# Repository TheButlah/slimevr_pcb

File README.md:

# slimevr_pcb
A collection of PCBs designed for SlimeVR full-body trackers

- [ferrous_slime](/hardware/ferrous_slime/) - A fully custom surface-mount PCB.
  Unlike most of the SlimeVR community, it uses the ESP32-C3, a newer and more
  powerful chip. Designed to be a more powerful development platform, as it natively
  supports JTAG debugging over USB, more compilers and languages, including Rust,
  and supports Bluetooth LE v5.0.
  
- [breakout_slime](/hardware/breakout_slime/) - A through-hole PCB for use with
  breakout boards. Simplest and easy to assemble by hand, but not as small of a
  form factor as it could be.

## License
**This hardware is licensed under the CERN-OHL-P v2 license**, which is a permissive,
non-viral and non-reciprocal open hardware license. Unlike software licenses like
MIT and Apache 2.0, it better handles the nuances of hardware and protects both
the licensor and licensee from patent lawsuits.

**Unless you explicitly state otherwise, any contribution intentionally submitted
for inclusion in this work by you, shall be licensed as above, without any
additional terms or conditions.**

### Conveying notice of License
Note that as part of the CERN-OHL-P v2 license, recipients of manufactured
hardware must also receive notice of the above license. One such
method of conveying the notice is to include a link to the original source repo,
or printing "Licensed under CERN-OHL-P v2" on the PCB silkscreen. For more info,
see [here](https://ohwr.org/project/cernohl/wikis/uploads/8a6b5d01f71c207c49493e4d114d61e6/cern_ohl_p_v2_howto.pdf).

This is conceptually similar to the MIT/Apache 2.0 Licenses, where the original
license must still be included as a notice even when the source is modified and
subsequently relicensed under different terms.

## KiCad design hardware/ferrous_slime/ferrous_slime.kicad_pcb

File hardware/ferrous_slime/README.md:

# Ferrous SlimeVR
This PCB design is intended as a production-ready (mostly) SMT design. Unlike
current SlimeVR designs by the community and the production batch that use the
ESP8266, this board uses the *very* new ESP32-C3 chip, which is better in almost
all respects than its predecessors.

The IMU is still a breakout board to better allow the community to experiment
with different IMU options.

## IMU Compatibility
This board was designed to work with the following IMU breakouts, via solder
jumpers that can reconfigure the board.
- BNO08X (Aliexpress GY-BNO08X and Adafruit BNO08X)
- MPU-6050 (Aliexpress GY-521)
- MPU-9250/6500 (Aliexpress GY-9250 and MPU-92/65)
- ICM20948 3.3v (Aliexpress GY-912 and Pimoroni PIM448)

## Renders

As always, check to make sure your particular breakout board has the pins in the
right spots for this PCB! Not all breakouts of the same IMU have the same pins!

## Why the ESP32-C3?
First and foremost, the ESP32-C3 uses RISC-V as its instruction set, rather than
XTensa. XTensa is not supported by LLVM (yet), or by the Rust programming language,
without using a [fork of the compiler](https://github.com/espressif/llvm-project).
I wanted to use this design in future IOT projects as well, so targeting a more
mainstream instruction set with better compiler support seems useful. It will also
help me more easily use Rust with this device!

Secondly, the ESP32-C3 is similar in features to the ESP32 series of chips, but like
the ESP8266, it is very cheap, making it a great choice. A few of the features it has
over the ESP8266:
- Bluetooth LE v5.0 (even ESP32 only has v4.2)
- Stronger WiFi signal at a lower power usage than the ESP8266
- More RAM (400KiB vs 160)
- Built-in USB-serial and USB-JTAG support eliminates need for USB-UART chip
- JTAG debugging
- Sleep modes consume *significantly* less power
- New peripherals like security modules
- GPIO is more fully featured, and has more pins

For more info, [this](https://hackaday.com/2021/02/08/hands-on-the-risc-v-esp32-c3-will-be-your-new-esp8266/)
was a good article.

## Changelog
A description of the changes in each revision can be found [here](CHANGELOG.md).

## Credits
The original v0.1.0 design was based on the schematics of the [esp-rs Rust board](https://github.com/esp-rs/esp-rust-board).
Thanks to the esp-rs community for being so awesome!
Also, thanks to the SlimeVR developers and especially @Eirenliel for making SlimeVR awesome and open source :)

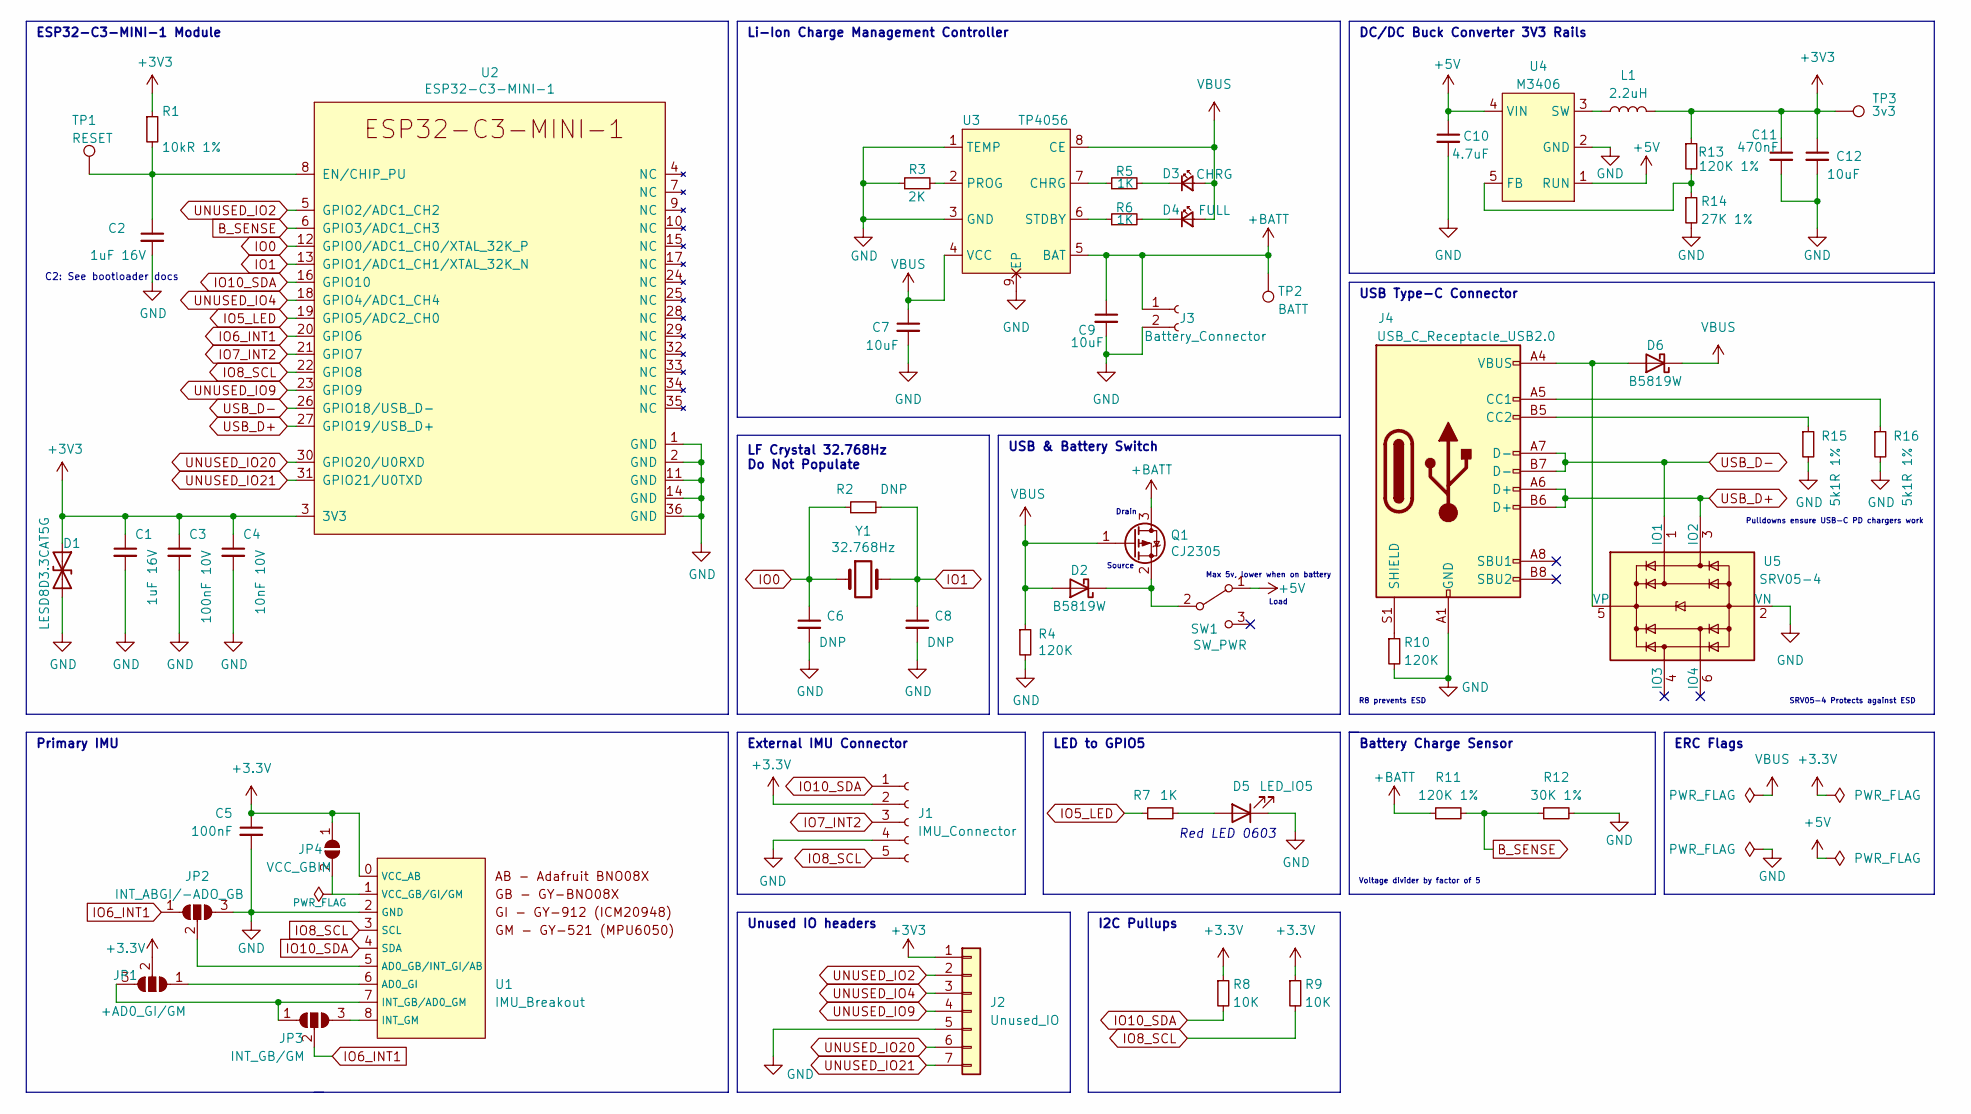
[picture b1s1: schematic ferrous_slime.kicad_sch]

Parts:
C1, C2: 1uF 16V; C_0603_1608Metric
C3: 100nF 10V; C_0603_1608Metric
C4: 10nF 10V; C_0603_1608Metric
C5: 100nF; C_0603_1608Metric
C6, C8: DNP; C_0603_1608Metric
C7, C9, C12: 10uF; C_0603_1608Metric
C10: 4.7uF; C_0603_1608Metric
C11: 470nF; C_0603_1608Metric
D1: LESD8D3.3CAT5G; SOD882
D2, D6: B5819W; D_SOD-123
D3: CHRG; LED_0603_1608Metric
D4: FULL; LED_0603_1608Metric
D5: LED_IO5; LED_0603_1608Metric
J1: IMU_Connector; JST_PH_S5B-PH-K_1x05_P2.00mm_Horizontal
J2: Unused_IO; IO_Breakouts
J3: Battery_Connector; JST_PH_S2B-PH-K_1x02_P2.00mm_Horizontal
J4: USB_C_Receptacle_USB2.0; USB_C_Receptacle_XKB_U262-16XN-4BVC11; PARTREV A3
JP1: +AD0_GI/GM; SolderJumper-3_P1.3mm_Open_Pad1.0x1.5mm
JP2: INT_ABGI/-ADO_GB; SolderJumper-3_P1.3mm_Open_Pad1.0x1.5mm
JP3: INT_GB/GM; SolderJumper-3_P1.3mm_Open_Pad1.0x1.5mm
JP4: VCC_GBIM; SolderJumper-2_P1.3mm_Open_RoundedPad1.0x1.5mm
L1: 2.2uH; L_Wuerth_MAPI-3015
Q1: CJ2305; SOT-23
R1: 10kR 1%; R_0603_1608Metric
R2: DNP; R_0603_1608Metric
R3: 2K; R_0603_1608Metric
R4, R10: 120K; R_0603_1608Metric
R5, R6, R7: 1K; R_0603_1608Metric
R8, R9: 10K; R_0603_1608Metric
R11, R13: 120K 1%; R_0603_1608Metric
R12: 30K 1%; R_0603_1608Metric
R14: 27K 1%; R_0603_1608Metric
R15, R16: 5k1R 1%; R_0603_1608Metric
SW1: SW_PWR; SW_CuK_OS102011MA1QN1_SPDT_Angled
TP1: RESET; TestPoint_Pad_D1.0mm
TP2: BATT; TestPoint_Pad_D1.0mm
TP3: 3v3; TestPoint_Pad_D1.0mm
U1: IMU_Breakout
U2: ESP32-C3-MINI-1
U3: TP4056; HTSOP-8-1EP_3.9x4.9mm_P1.27mm_EP2.4x3.2mm
U4: M3406; SOT-23-5
U5: SRV05-4; SOT-23-6
Y1: 32.768Hz; Crystal_SMD_3215-2Pin_3.2x1.5mm

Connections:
+5V: C10.1, SW1.1 (A), U4.1 (RUN), U4.4 (VIN)
+BATT: C9.1, J3.1, Q1.3 (D), R11.1, TP2.1, U3.5 (BAT)
B_SENSE: R11.2, R12.1, U2.6 (GPIO3/ADC1_CH3)
GND: C1.2, C2.2, C3.2, C4.2, C5.2, C6.2, C7.2, C8.2, C9.2, C10.2, C11.2, C12.2, D1.2 (A2), D5.1 (K), J1.4, J2.5, J3.2, J4.A1 (GND), J4.A12 (GND), J4.B1 (GND), J4.B12 (GND), JP2.3 (B), R3.1, R4.2, R10.2, R12.2, R14.2, R15.2, R16.2, U1.2 (GND), U2.1 (GND), U2.2 (GND), U2.11 (GND), U2.14 (GND), U2.36 (GND), U3.1 (TEMP), U3.3 (GND), U3.9 (EP), U4.2 (GND), U5.2 (VN)
IO0: C6.1, R2.1, U2.12 (GPIO0/ADC1_CH0/XTAL_32K_P), Y1.1
IO1: C8.1, R2.2, U2.13 (GPIO1/ADC1_CH1/XTAL_32K_N), Y1.2
IO5_LED: R7.1, U2.19 (GPIO5/ADC2_CH0)
IO6_INT1: JP2.1 (A), JP3.2 (C), U2.20 (GPIO6)
IO7_INT2: J1.3, U2.21 (GPIO7)
IO8_SCL: J1.5, R9.2, U1.3 (SCL), U2.22 (GPIO8)
IO10_SDA: J1.1, R8.2, U1.4 (SDA), U2.16 (GPIO10)
unnamed: C2.1, R1.2, TP1.1, U2.8 (EN/CHIP_PU)
unnamed: D2.1 (K), Q1.2 (S), SW1.2 (B)
unnamed: D3.1 (K), R5.2
unnamed: D4.1 (K), R6.2
unnamed: D5.2 (A), R7.2
unnamed: D6.2 (A), J4.A4 (VBUS), J4.A9 (VBUS), J4.B4 (VBUS), J4.B9 (VBUS), U5.5 (VP)
unnamed: J4.A5 (CC1), R16.1
unnamed: J4.B5 (CC2), R15.1
unnamed: J4.S1 (SHIELD), R10.1
unnamed: JP1.1 (A), U1.6 (AD0_GI)
unnamed: JP1.3 (B), JP3.1 (A), U1.7 (INT_GB/AD0_GM)
unnamed: JP2.2 (C), U1.5 (AD0_GB/INT_GI/AB)
unnamed: JP3.3 (B), U1.8 (INT_GM)
unnamed: JP4.2 (B), U1.1 (VCC_GB/GI/GM)
unnamed: L1.1, U4.3 (SW)
unnamed: R3.2, U3.2 (PROG)
unnamed: R5.1, U3.7 (CHRG)
unnamed: R6.1, U3.6 (STDBY)
unnamed: R13.2, R14.1, U4.5 (FB)
UNUSED_IO2: J2.2, U2.5 (GPIO2/ADC1_CH2)
UNUSED_IO4: J2.3, U2.18 (GPIO4/ADC1_CH4)
UNUSED_IO9: J2.4, U2.23 (GPIO9)
UNUSED_IO20: J2.6, U2.30 (GPIO20/U0RXD)
UNUSED_IO21: J2.7, U2.31 (GPIO21/U0TXD)
USB_D+: J4.A6 (D+), J4.B6 (D+), U2.27 (GPIO19/USB_D+), U5.3 (IO2)
USB_D-: J4.A7 (D-), J4.B7 (D-), U2.26 (GPIO18/USB_D-), U5.1 (IO1)
VBUS: C7.1, D2.2 (A), D3.2 (A), D4.2 (A), D6.1 (K), Q1.1 (G), R4.1, U3.4 (VCC), U3.8 (CE)

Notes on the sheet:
Voltage divider by factor of 5
USB Type-C Connector
Max 5v, lower when on battery
Drain
ERC Flags
LF Crystal 32.768Hz Do Not Populate
External IMU Connector
Source
DC/DC Buck Converter 3V3 Rails
Red LED 0603
USB & Battery Switch
R8 prevents ESD
Battery Charge Sensor
LED to GPIO5
Load
SRV05-4 Protects against ESD
Unused IO headers
Primary IMU
ESP32-C3-MINI-1 Module
Li-Ion Charge Management Controller
Pulldowns ensure USB-C PD chargers work
I2C Pullups
C2: See bootloader docs

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
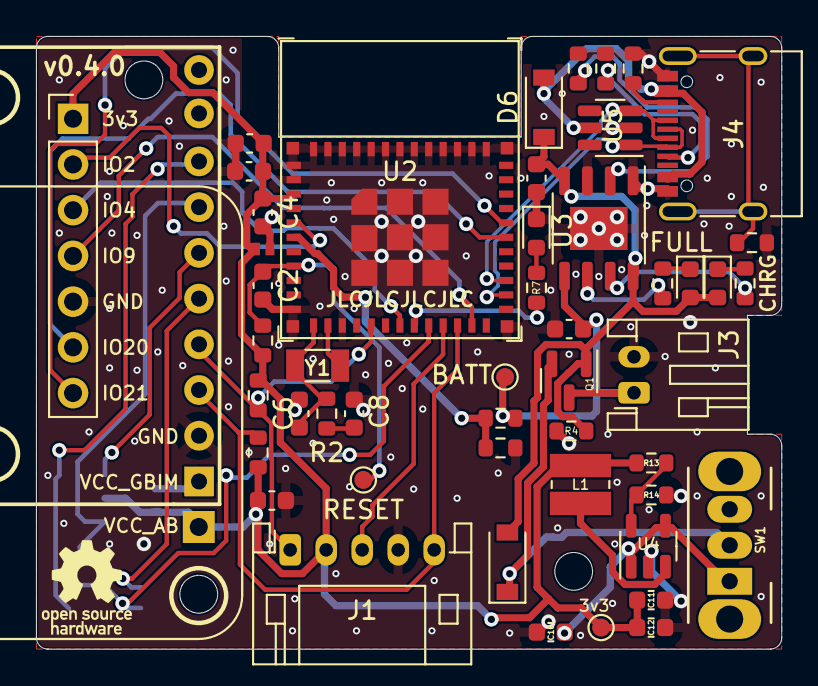
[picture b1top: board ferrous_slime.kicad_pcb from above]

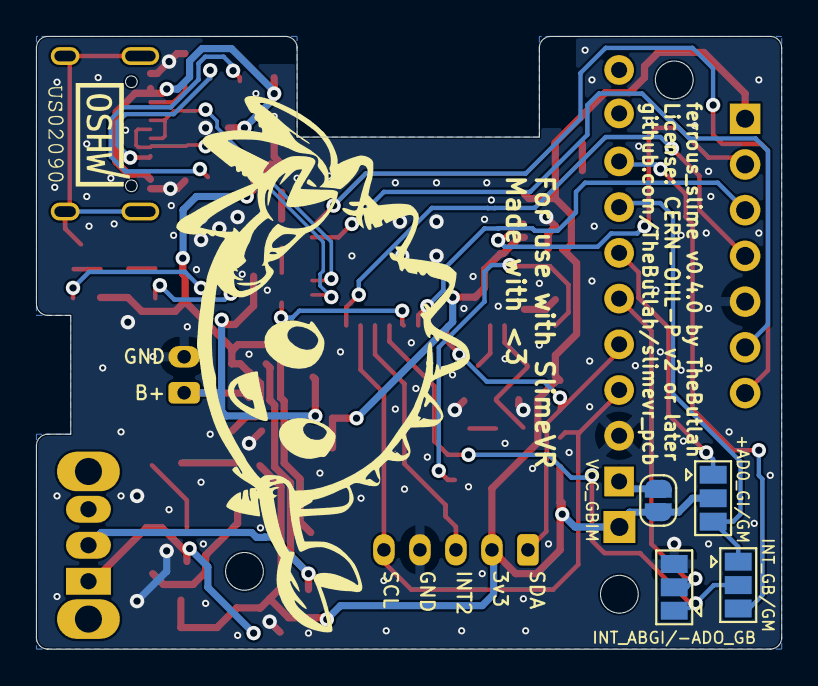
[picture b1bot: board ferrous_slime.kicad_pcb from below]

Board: 2 copper layers, 41.4 x 34.0 mm, 57 parts (4 on the bottom side), 39 nets.

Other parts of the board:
H1, H2, H3: MountingHole_2.1mm

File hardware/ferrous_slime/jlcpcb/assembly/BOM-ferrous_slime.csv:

Comment,Designator,Footprint,LCSC
100nF 10V,"C3,C5",C_0603_1608Metric,C14663
1uF 16V,"C1,C2",C_0603_1608Metric,C15849
470nF,C11,C_0603_1608Metric,C1623
TP4056,U3,HTSOP-8-1EP_3.9x4.9mm_P1.27mm_EP2.4x3.2mm,C16581
LESD8D3.3CAT5G,D1,SOD882,C172409
4.7uF,C10,C_0603_1608Metric,C19666
10uF,"C12,C7,C9",C_0603_1608Metric,C19702
2.2uH,L1,L_Wuerth_MAPI-3015,C19734
1K,"R5,R6,R7",R_0603_1608Metric,C21190
CHRG,D3,LED_0603_1608Metric,C2286
27K 1%,R14,R_0603_1608Metric,C22967
2K,R3,R_0603_1608Metric,C22975
30K 1%,R12,R_0603_1608Metric,C22984
5k1R 1%,"R15,R16",R_0603_1608Metric,C23186
10kR 1%,"R1,R8,R9",R_0603_1608Metric,C25804
120K,"R10,R11,R13,R4",R_0603_1608Metric,C25808
ESP32-C3-MINI-1,U2,ESP32-C3-MINI-1,C2838502
USB_C_Receptacle_USB2.0,J4,USB_C_Receptacle_XKB_U262-16XN-4BVC11,C319148
10nF 10V,C4,C_0603_1608Metric,C57112
LED_IO5,D5,LED_0603_1608Metric,C72038
FULL,D4,LED_0603_1608Metric,C72043
M3406,U4,SOT-23-5,C83224
SRV05-4,U5,SOT-23-6,C85364
CJ2305,Q1,SOT-23,C8549
B5819W,"D2,D6",D_SOD-123,C8598
IMU_Connector,J1,JST_PH_S5B-PH-K_1x05_P2.00mm_Horizontal,
3v3,TP3,TestPoint_Pad_D1.0mm,
Battery_Connector,J3,JST_PH_S2B-PH-K_1x02_P2.00mm_Horizontal,
SW_PWR,SW1,SW_CuK_OS102011MA1QN1_SPDT_Angled,
+AD0_GI/GM,JP1,SolderJumper-3_P1.3mm_Open_Pad1.0x1.5mm,
IMU_Breakout,U1,IMU_Breakout,
BATT,TP2,TestPoint_Pad_D1.0mm,
INT_GB/GM,JP3,SolderJumper-3_P1.3mm_Open_Pad1.0x1.5mm,
INT_ABGI/-ADO_GB,JP2,SolderJumper-3_P1.3mm_Open_Pad1.0x1.5mm,
DNP,R2,R_0603_1608Metric,
Unused_IO,J2,IO_Breakouts,
VCC_GBIM,JP4,SolderJumper-2_P1.3mm_Open_RoundedPad1.0x1.5mm,
RESET,TP1,TestPoint_Pad_D1.0mm,

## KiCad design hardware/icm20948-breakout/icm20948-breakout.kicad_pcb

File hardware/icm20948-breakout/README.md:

# ICM-20948 Breakout for `ferrous_slime`
This is a breakout board for the [ICM-20948](https://invensense.tdk.com/products/motion-tracking/9-axis/icm-20948/) IMU, targeting the [`ferrous_slime` board by TheButlah](https://github.com/TheButlah/slimevr_pcb/tree/main/hardware/ferrous_slime).  It contains a voltage translator to allow 1.8v<->3.3v communication between the IMU and the ESP.

The pin socket is optional and only serves to allow rapid prototyping of the board.  Final revisions may be directly soldered to the `ferrous_slime` or attached via a double-sided pin header.

*Note: This breakout is currently being tested and may not work as intended.*

## Renders

## Thanks
- [dtornqvist](https://github.com/dtornqvist/icm-20948-breakout) for a part list and implementation reference

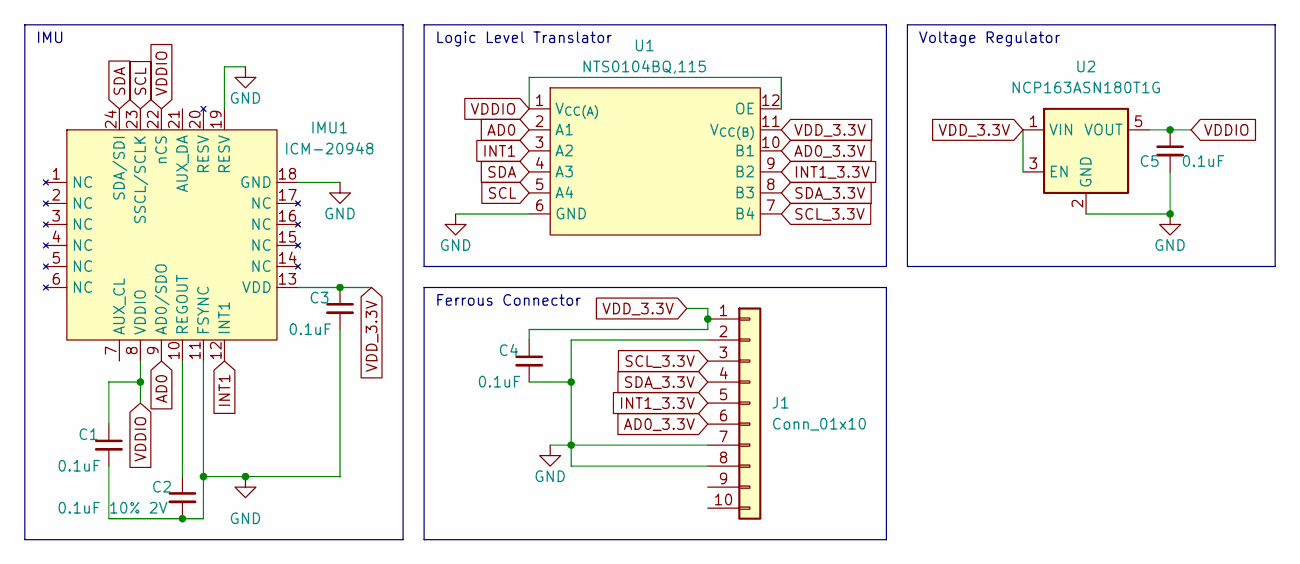
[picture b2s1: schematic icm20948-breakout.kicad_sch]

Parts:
C1, C3, C4, C5: 0.1uF; C_0603_1608Metric
C2: 0.1uF 10% 2V; C_0603_1608Metric
IMU1: ICM-20948; QFN-24-1EP_3x3mm_P0.4mm_EP1.75x1.6mm
J1: Conn_01x10; PinSocket_1x10_P2.54mm_Vertical
U1: NTS0104BQ,115; XQFN12
U2: NCP163ASN180T1G; SOT-23-5

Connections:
AD0: IMU1.9 (AD0/SDO), U1.2 (A1)
AD0_3.3V: J1.6, U1.10 (B1)
GND: C1.2, C2.2, C3.2, C4.2, C5.2, IMU1.11 (FSYNC), IMU1.18 (GND), IMU1.19 (RESV), J1.2, J1.7, J1.8, U1.6 (GND), U2.2 (GND)
INT1: IMU1.12 (INT1), U1.3 (A2)
INT1_3.3V: J1.5, U1.9 (B2)
unnamed: C2.1, IMU1.10 (REGOUT)
SCL: IMU1.23 (SSCL/SCLK), U1.5 (A4)
SCL_3.3V: J1.3, U1.7 (B4)
SDA: IMU1.24 (SDA/SDI), U1.4 (A3)
SDA_3.3V: J1.4, U1.8 (B3)
VDDIO: C1.1, C5.1, IMU1.8 (VDDIO), IMU1.22 (nCS), U1.1 (V_{CC(A)}), U1.12 (OE), U2.5 (VOUT)
VDD_3.3V: C3.1, C4.1, IMU1.13 (VDD), J1.1, U1.11 (V_{CC(B)}), U2.1 (VIN), U2.3 (EN)

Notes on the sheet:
Voltage Regulator
IMU
Ferrous Connector
Logic Level Translator

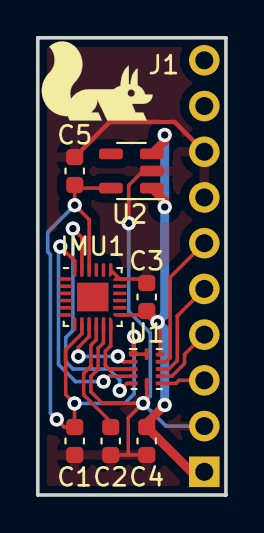
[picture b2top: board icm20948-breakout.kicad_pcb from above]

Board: 2 copper layers, 10.5 x 25.4 mm, 9 parts (1 on the bottom side), 12 nets.

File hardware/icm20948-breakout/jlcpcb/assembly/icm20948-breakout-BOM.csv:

Comment,Designator,Footprint
NCP163ASN180T1G,U2,SOT-23-5
0.1uF 10% 2V,C2,C_0603_1608Metric
0.1uF,"C5,C4,C1,C3",C_0603_1608Metric
"NTS0104BQ,115",U1,XQFN12
ICM-20948,IMU1,QFN-24-1EP_3x3mm_P0.4mm_EP1.75x1.6mm
Conn_01x10,J1,PinSocket_1x10_P2.54mm_Vertical

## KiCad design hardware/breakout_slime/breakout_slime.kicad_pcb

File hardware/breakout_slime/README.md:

# Breakout SlimeVR
This PCB design is intended as the easiest DIY SlimeVR pcb. It is a simple two
layer PCB, and should make assembling SlimeVR significantly easier than using a
protoboard.

**NOTE: This has only been tested on BNOs and MPUs.**
Also, use it at your own risk. I've tested it, but I accept no responsibility for it ;)

## Renders

## Changelog
A description of the changes in each revision can be found [here](CHANGELOG.md).

## How to order
You can place a jlcpcb order by uploading the [zip file](jlcpcb/gerber/GERBER-breakout_slime.zip) for the gerbers. Take that zip file and upload to https://jlcpcb.com.

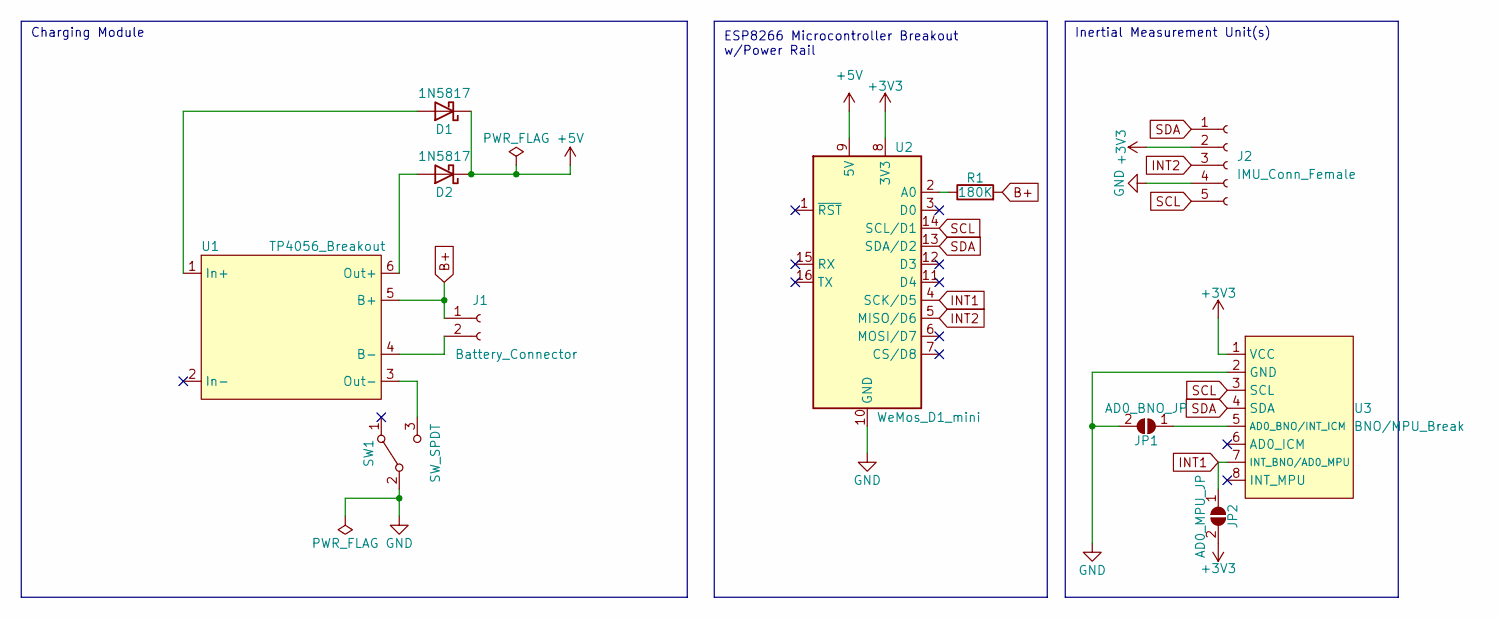
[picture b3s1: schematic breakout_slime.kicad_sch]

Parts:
D1, D2: 1N5817; D_DO-41_SOD81_P10.16mm_Horizontal
J1: Battery_Connector; JST_PH_S2B-PH-K_1x02_P2.00mm_Horizontal
J2: IMU_Conn_Female; JST_PH_S5B-PH-K_1x05_P2.00mm_Horizontal
JP1: AD0_BNO_JP; SolderJumper-2_P1.3mm_Open_Pad1.0x1.5mm
JP2: AD0_MPU_JP; SolderJumper-2_P1.3mm_Open_Pad1.0x1.5mm
R1: 180K; R_Axial_DIN0207_L6.3mm_D2.5mm_P10.16mm_Horizontal
SW1: SW_SPDT; SW_CuK_OS102011MA1QN1_SPDT_Angled
U1: TP4056_Breakout
U2: WeMos_D1_mini; WEMOS_D1_mini_light
U3: BNO/MPU_Break; BNO_MPU_ICM_Breakout

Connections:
+3V3: J2.2, JP2.2 (B), U2.8 (3V3), U3.1 (VCC)
+5V: D1.1 (K), D2.1 (K), U2.9 (5V)
B+: J1.1, R1.2, U1.5 (B+)
GND: J2.4, JP1.2 (B), SW1.2 (B), U2.10 (GND), U3.2 (GND)
INT1: JP2.1 (A), U2.4 (SCK/D5), U3.7 (INT_BNO/AD0_MPU)
INT2: J2.3, U2.5 (MISO/D6)
unnamed: D1.2 (A), U1.1 (In+)
unnamed: D2.2 (A), U1.6 (Out+)
unnamed: J1.2, U1.4 (B-)
unnamed: JP1.1 (A), U3.5 (AD0_BNO/INT_ICM)
unnamed: R1.1, U2.2 (A0)
unnamed: SW1.3 (C), U1.3 (Out-)
SCL: J2.5, U2.14 (SCL/D1), U3.3 (SCL)
SDA: J2.1, U2.13 (SDA/D2), U3.4 (SDA)

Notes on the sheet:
Charging Module
ESP8266 Microcontroller Breakout w/Power Rail
Inertial Measurement Unit(s)

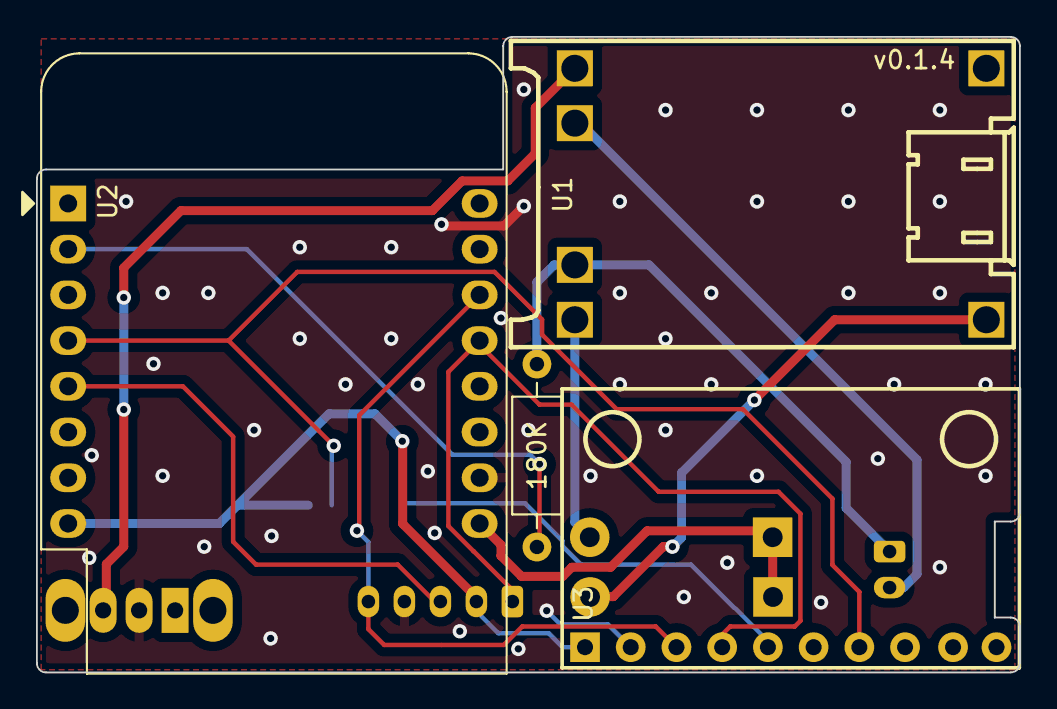
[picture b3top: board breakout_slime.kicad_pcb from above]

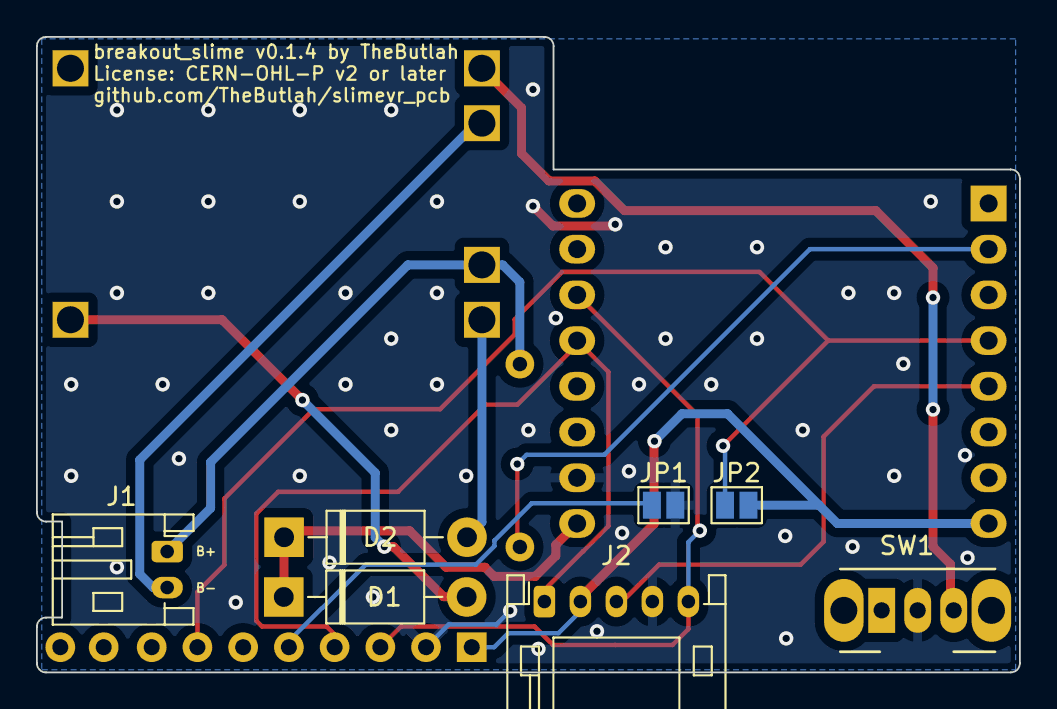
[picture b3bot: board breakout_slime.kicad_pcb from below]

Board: 2 copper layers, 54.6 x 35.3 mm, 11 parts (7 on the bottom side), 14 nets.

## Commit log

2022-02-24 Finished schematic
2022-02-24 Assigned Footprints
2022-02-27 Added TP4056 breakout and assigned more footprints
2022-02-27 Added BNO_MPU_Breakout
2022-02-27 Added comment about the status of the board
2022-02-27 Finished board rev 0.1
2022-02-27 Generated Gerbers
2022-03-01 Started esp32c3_slime
2022-03-02 Switched charger to TP4056
2022-03-03 Switched power system to M3406
2022-03-04 Renamed to ferrous_slime, fixed USBC, removed headers
2022-03-05 Added IMUs and resolved ERC
2022-03-05 Plotted schematic
2022-03-05 Removed I2C pullups since they are already in breakouts
2022-03-05 Added README.md for ferrous_slime
2022-03-05 Updated documentation
2022-03-07 Assigned most footprints
2022-03-07 Assigned remaining footprints, did layout
2022-03-07 Routed all nets, fixed most of silkscreen
2022-03-07 Added fab files
2022-03-07 Fixed battery connector polarity on breakout_slime
2022-03-08 Removed gerbers, made some minor tweaks to board layout
2022-03-10 Optimized signal traces and ground fills
2022-03-11 Filled in ground planes, updated version number, added Changelog
2022-03-13 breakout_slime v0.1.2
2022-03-13 Fixed D1 Mini model and added renders
2022-03-14 Added battery sense to ferrous_slime
2022-03-14 Added breakouts for remaining unused IO
2022-03-15 Fixed jumper silkscreens and added double ground plane
2022-03-15 Annotated pins and added silkscreen art
2022-03-15 Removed Rust_Board and updated all renders/plots
2022-03-15 ferrous_slime v0.0.1, generated gerbers
2022-03-16 Added refs to silkscreen
2022-03-17 v0.1.0 board released
2022-03-17 Add image of PCB layout
2022-03-19 Add images to main README
2022-04-06 Fixed rev # typo on schematic
2022-04-13 [breakout_slime] Released v0.1.3
2022-04-13 [breakout_slime] generated gerbers
2022-04-13 [breakout_slime] Fixed wrong slash type in gerber file path
2022-04-13 [breakout_slime] Updated disclaimer
2022-05-24 [breakout_slime] Fixed symbol/footprint lib paths
2022-05-24 fix link to CERN-OHL-P v2 user guide
2022-05-26 [breakout_slime] Released v0.1.4
2022-07-06 Added Cases for the BreakoutSlime PCB
2022-07-06 Tweaked PR
2022-07-06 Now tracking f3z and 3mf in git-lfs
2022-07-06 Added Cases for the BreakoutSlime PCB (#15)
    * Added Cases for the BreakoutSlime PCB
    * Tweaked PR
2022-07-11 Added Butter Dish Cases
2022-07-11 Added Butter Dish Cases (#18)
2022-09-09 Add icm20948 breakout
2022-09-09 Add documentation
2022-09-10 Update hardware/icm20948-breakout/NOTICE
2022-09-13 [WIP] ICM-20948 breakout (#19)
    * Add icm20948 breakout
    * Add documentation
    * Update hardware/icm20948-breakout/NOTICE
2022-10-10 Updated PCB to add second power pin
2022-10-10 Added adafruit bno to footprint
2022-10-11 Finished pcb for ferrous_slime v0.2.0
2022-10-11 ferrous_slime: 0.2.0 (#20)
2022-10-12 ferrous_slime: v0.3.0
2023-01-11 Now using srv05-4 and i2c pullups
2023-01-11 Lots of pcb progress
2023-01-11 Finished work
2023-01-11 ferrous_slime v0.4.0
2023-01-11 ferrous_slime v0.4.0 (#21)
2023-01-15 Added adafruit bno step file
2023-04-07 Started schematic for icm

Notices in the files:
hardware/breakout_slime/breakout_slime.kicad_pcb:
Licensed under CERN-OHL-P v2 or later
License: CERN-OHL-P v2 or later
